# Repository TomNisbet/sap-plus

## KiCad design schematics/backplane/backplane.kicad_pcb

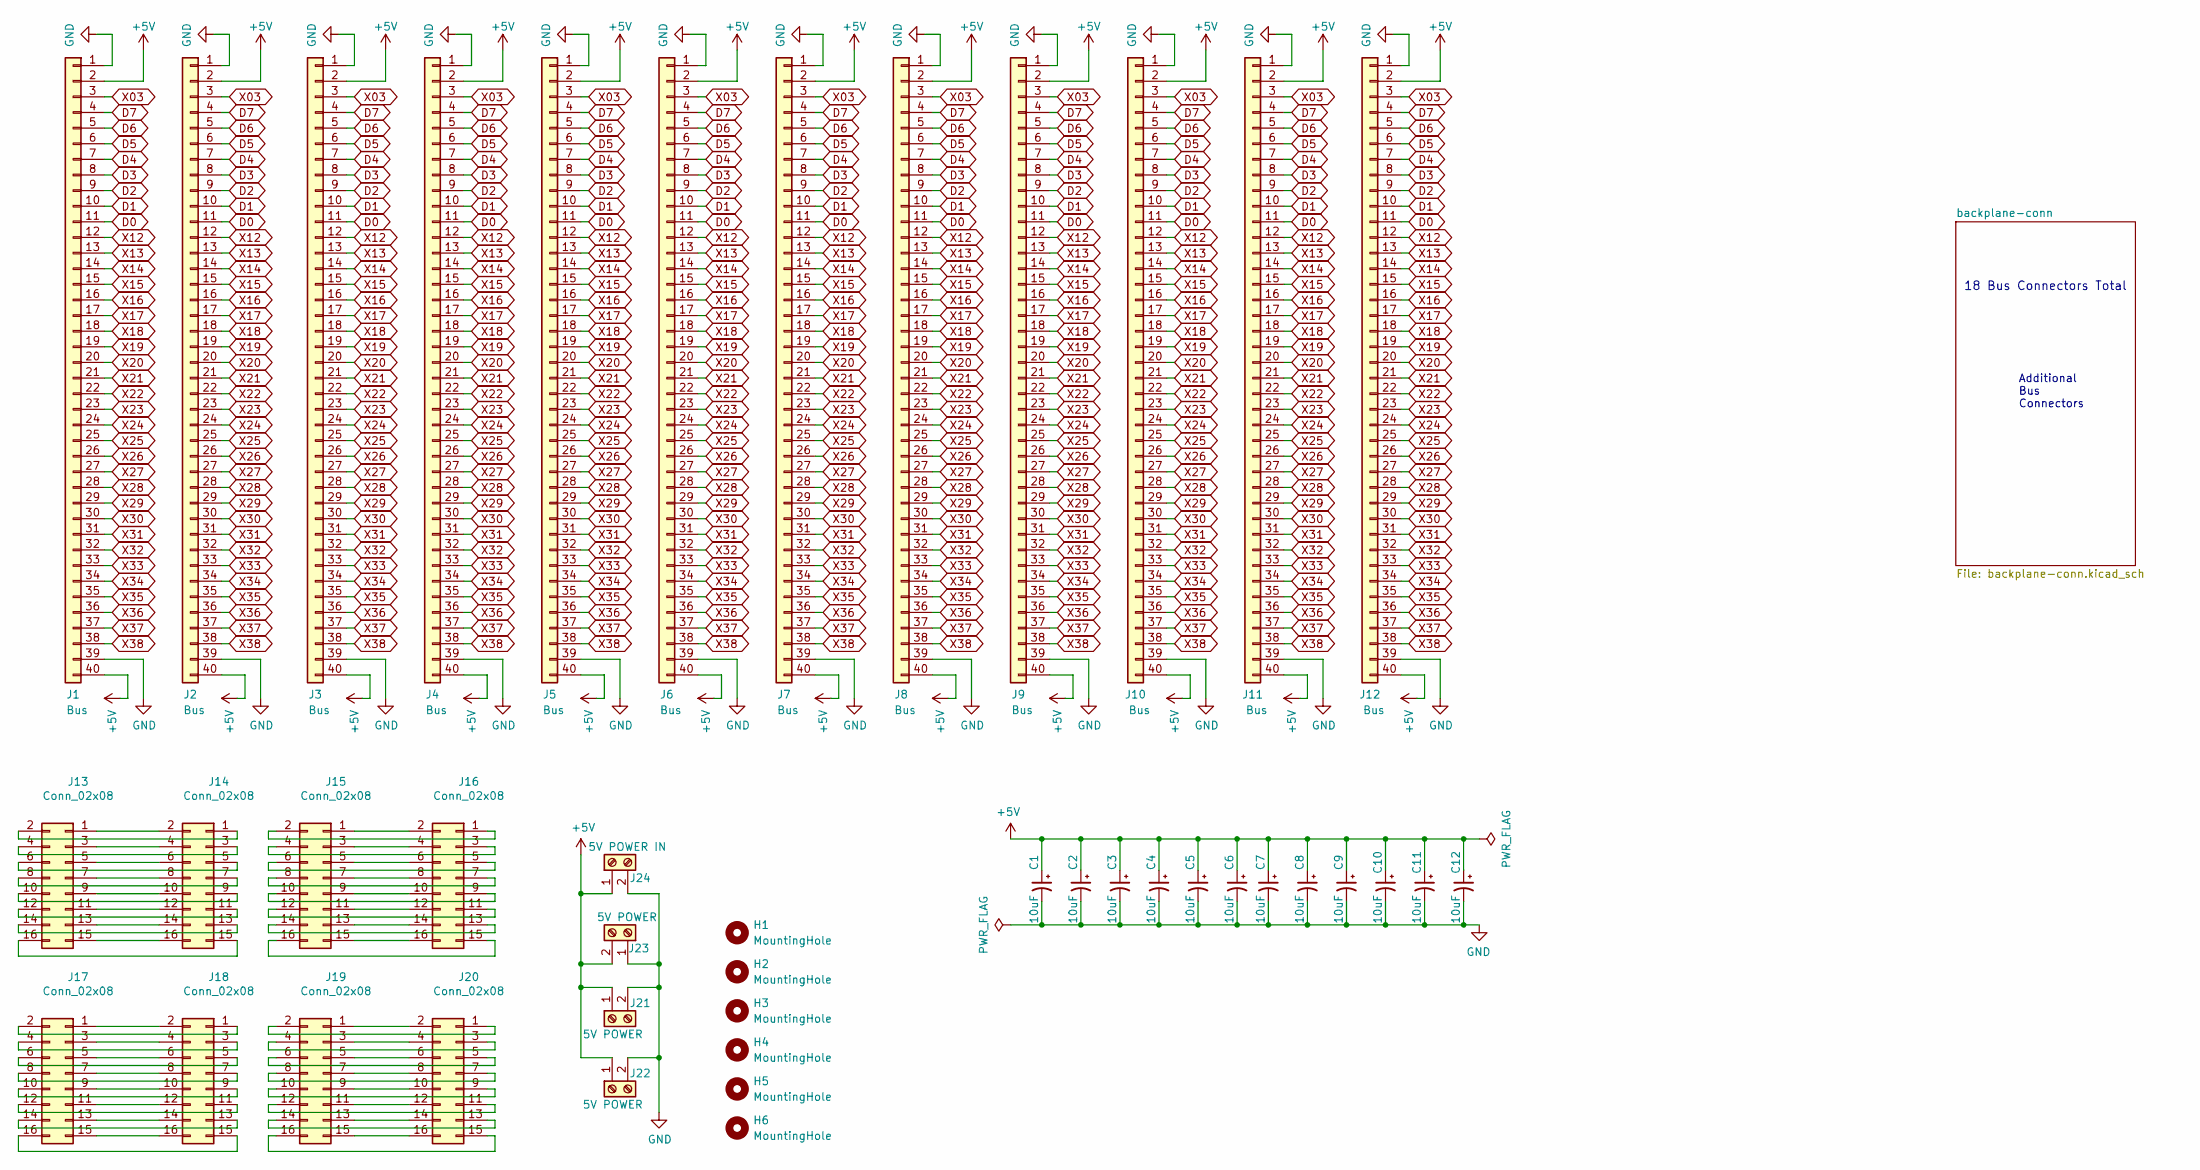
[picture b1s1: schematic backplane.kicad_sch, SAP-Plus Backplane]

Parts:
C1, C2, C3, C4, C5, C6, C7, C8, C9, C10, C11, C12: 10uF; C_Radial_D4.0mm_H5.0mm_P1.50mm
H1, H2, H3, H4, H5, H6: MountingHole; MountingHole_3.2mm_M3
J1, J2, J3, J4, J5, J6, J7, J8, J9, J10, J11, J12: Bus; PinSocket_1x40_P2.54mm_Vertical
J13, J14, J15, J16, J17, J18, J19, J20: Conn_02x08; PinSocket_2x08_P2.54mm_Vertical
J21, J22, J23: 5V POWER; TerminalBlock_RND_205-00012_1x02_P5.00mm_Horizontal
J24: 5V POWER IN; BarrelJack_Wuerth_6941xx301002

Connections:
+5V: C1.1, C2.1, C3.1, C4.1, C5.1, C6.1, C7.1, C8.1, C9.1, C10.1, C11.1, C12.1, J1.2, J1.40, J2.2, J2.40, J3.2, J3.40, J4.2, J4.40, J5.2, J5.40, J6.2, J6.40, J7.2, J7.40, J8.2, J8.40, J9.2, J9.40, J10.2, J10.40, J11.2, J11.40, J12.2, J12.40, J21.1, J22.1, J23.2, J24.1
D0: J1.11, J2.11, J3.11, J4.11, J5.11, J6.11, J7.11, J8.11, J9.11, J10.11, J11.11, J12.11
D1: J1.10, J2.10, J3.10, J4.10, J5.10, J6.10, J7.10, J8.10, J9.10, J10.10, J11.10, J12.10
D2: J1.9, J2.9, J3.9, J4.9, J5.9, J6.9, J7.9, J8.9, J9.9, J10.9, J11.9, J12.9
D3: J1.8, J2.8, J3.8, J4.8, J5.8, J6.8, J7.8, J8.8, J9.8, J10.8, J11.8, J12.8
D4: J1.7, J2.7, J3.7, J4.7, J5.7, J6.7, J7.7, J8.7, J9.7, J10.7, J11.7, J12.7
D5: J1.6, J2.6, J3.6, J4.6, J5.6, J6.6, J7.6, J8.6, J9.6, J10.6, J11.6, J12.6
D6: J1.5, J2.5, J3.5, J4.5, J5.5, J6.5, J7.5, J8.5, J9.5, J10.5, J11.5, J12.5
D7: J1.4, J2.4, J3.4, J4.4, J5.4, J6.4, J7.4, J8.4, J9.4, J10.4, J11.4, J12.4
GND: C1.2, C2.2, C3.2, C4.2, C5.2, C6.2, C7.2, C8.2, C9.2, C10.2, C11.2, C12.2, J1.1, J1.39, J2.1, J2.39, J3.1, J3.39, J4.1, J4.39, J5.1, J5.39, J6.1, J6.39, J7.1, J7.39, J8.1, J8.39, J9.1, J9.39, J10.1, J10.39, J11.1, J11.39, J12.1, J12.39, J21.2, J22.2, J23.1, J24.2
unnamed: J13.1, J14.2
unnamed: J13.2, J14.1
unnamed: J13.3, J14.4
unnamed: J13.4, J14.3
unnamed: J13.5, J14.6
unnamed: J13.6, J14.5
unnamed: J13.7, J14.8
unnamed: J13.8, J14.7
unnamed: J13.9, J14.10
unnamed: J13.10, J14.9
unnamed: J13.11, J14.12
unnamed: J13.12, J14.11
unnamed: J13.13, J14.14
unnamed: J13.14, J14.13
unnamed: J13.15, J14.16
unnamed: J13.16, J14.15
unnamed: J15.1, J16.2
unnamed: J15.2, J16.1
unnamed: J15.3, J16.4
unnamed: J15.4, J16.3
unnamed: J15.5, J16.6
unnamed: J15.6, J16.5
unnamed: J15.7, J16.8
unnamed: J15.8, J16.7
unnamed: J15.9, J16.10
unnamed: J15.10, J16.9
unnamed: J15.11, J16.12
unnamed: J15.12, J16.11
unnamed: J15.13, J16.14
unnamed: J15.14, J16.13
unnamed: J15.15, J16.16
unnamed: J15.16, J16.15
unnamed: J17.1, J18.2
unnamed: J17.2, J18.1
unnamed: J17.3, J18.4
unnamed: J17.4, J18.3
unnamed: J17.5, J18.6
unnamed: J17.6, J18.5
unnamed: J17.7, J18.8
unnamed: J17.8, J18.7
unnamed: J17.9, J18.10
unnamed: J17.10, J18.9
unnamed: J17.11, J18.12
unnamed: J17.12, J18.11
unnamed: J17.13, J18.14
unnamed: J17.14, J18.13
unnamed: J17.15, J18.16
unnamed: J17.16, J18.15
unnamed: J19.1, J20.2
unnamed: J19.2, J20.1
unnamed: J19.3, J20.4
unnamed: J19.4, J20.3
unnamed: J19.5, J20.6
unnamed: J19.6, J20.5
unnamed: J19.7, J20.8
unnamed: J19.8, J20.7
unnamed: J19.9, J20.10
unnamed: J19.10, J20.9
unnamed: J19.11, J20.12
unnamed: J19.12, J20.11
unnamed: J19.13, J20.14
unnamed: J19.14, J20.13
unnamed: J19.15, J20.16
unnamed: J19.16, J20.15
X03: J1.3, J2.3, J3.3, J4.3, J5.3, J6.3, J7.3, J8.3, J9.3, J10.3, J11.3, J12.3
X12: J1.12, J2.12, J3.12, J4.12, J5.12, J6.12, J7.12, J8.12, J9.12, J10.12, J11.12, J12.12
X13: J1.13, J2.13, J3.13, J4.13, J5.13, J6.13, J7.13, J8.13, J9.13, J10.13, J11.13, J12.13
X14: J1.14, J2.14, J3.14, J4.14, J5.14, J6.14, J7.14, J8.14, J9.14, J10.14, J11.14, J12.14
X15: J1.15, J2.15, J3.15, J4.15, J5.15, J6.15, J7.15, J8.15, J9.15, J10.15, J11.15, J12.15
X16: J1.16, J2.16, J3.16, J4.16, J5.16, J6.16, J7.16, J8.16, J9.16, J10.16, J11.16, J12.16
X17: J1.17, J2.17, J3.17, J4.17, J5.17, J6.17, J7.17, J8.17, J9.17, J10.17, J11.17, J12.17
X18: J1.18, J2.18, J3.18, J4.18, J5.18, J6.18, J7.18, J8.18, J9.18, J10.18, J11.18, J12.18
X19: J1.19, J2.19, J3.19, J4.19, J5.19, J6.19, J7.19, J8.19, J9.19, J10.19, J11.19, J12.19
X20: J1.20, J2.20, J3.20, J4.20, J5.20, J6.20, J7.20, J8.20, J9.20, J10.20, J11.20, J12.20
X21: J1.21, J2.21, J3.21, J4.21, J5.21, J6.21, J7.21, J8.21, J9.21, J10.21, J11.21, J12.21
X22: J1.22, J2.22, J3.22, J4.22, J5.22, J6.22, J7.22, J8.22, J9.22, J10.22, J11.22, J12.22
X23: J1.23, J2.23, J3.23, J4.23, J5.23, J6.23, J7.23, J8.23, J9.23, J10.23, J11.23, J12.23
X24: J1.24, J2.24, J3.24, J4.24, J5.24, J6.24, J7.24, J8.24, J9.24, J10.24, J11.24, J12.24
X25: J1.25, J2.25, J3.25, J4.25, J5.25, J6.25, J7.25, J8.25, J9.25, J10.25, J11.25, J12.25
X26: J1.26, J2.26, J3.26, J4.26, J5.26, J6.26, J7.26, J8.26, J9.26, J10.26, J11.26, J12.26
X27: J1.27, J2.27, J3.27, J4.27, J5.27, J6.27, J7.27, J8.27, J9.27, J10.27, J11.27, J12.27
X28: J1.28, J2.28, J3.28, J4.28, J5.28, J6.28, J7.28, J8.28, J9.28, J10.28, J11.28, J12.28
X29: J1.29, J2.29, J3.29, J4.29, J5.29, J6.29, J7.29, J8.29, J9.29, J10.29, J11.29, J12.29
X30: J1.30, J2.30, J3.30, J4.30, J5.30, J6.30, J7.30, J8.30, J9.30, J10.30, J11.30, J12.30
X31: J1.31, J2.31, J3.31, J4.31, J5.31, J6.31, J7.31, J8.31, J9.31, J10.31, J11.31, J12.31
X32: J1.32, J2.32, J3.32, J4.32, J5.32, J6.32, J7.32, J8.32, J9.32, J10.32, J11.32, J12.32
X33: J1.33, J2.33, J3.33, J4.33, J5.33, J6.33, J7.33, J8.33, J9.33, J10.33, J11.33, J12.33
X34: J1.34, J2.34, J3.34, J4.34, J5.34, J6.34, J7.34, J8.34, J9.34, J10.34, J11.34, J12.34
X35: J1.35, J2.35, J3.35, J4.35, J5.35, J6.35, J7.35, J8.35, J9.35, J10.35, J11.35, J12.35
X36: J1.36, J2.36, J3.36, J4.36, J5.36, J6.36, J7.36, J8.36, J9.36, J10.36, J11.36, J12.36
X37: J1.37, J2.37, J3.37, J4.37, J5.37, J6.37, J7.37, J8.37, J9.37, J10.37, J11.37, J12.37
X38: J1.38, J2.38, J3.38, J4.38, J5.38, J6.38, J7.38, J8.38, J9.38, J10.38, J11.38, J12.38

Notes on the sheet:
Additional Bus Connectors
18 Bus Connectors Total

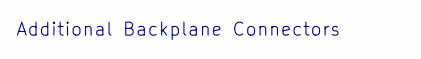
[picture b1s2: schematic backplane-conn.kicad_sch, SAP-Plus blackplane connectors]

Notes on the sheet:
Additional Backplane Connectors

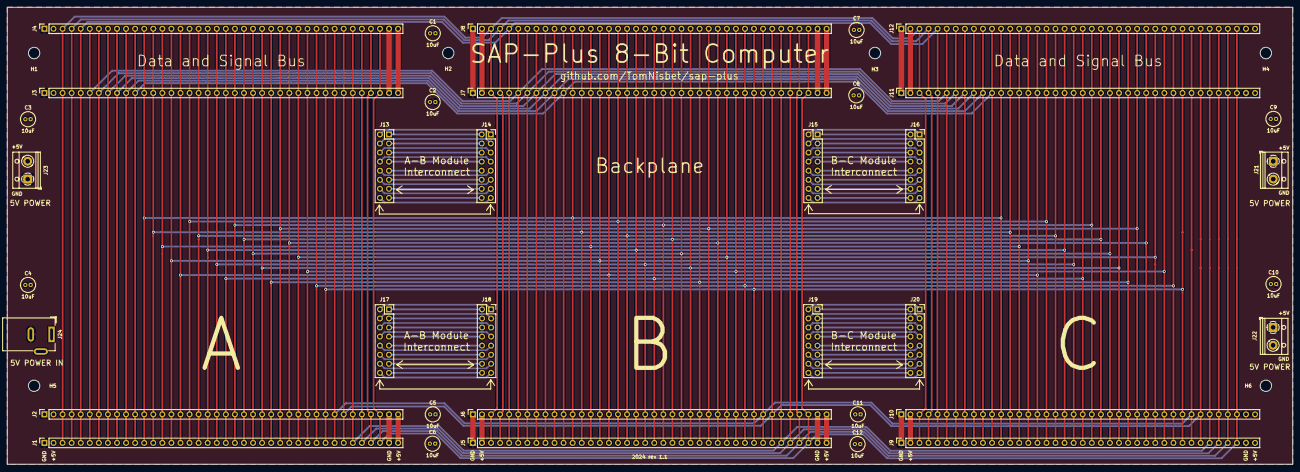
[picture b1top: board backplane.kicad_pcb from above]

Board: 2 copper layers, 360.0 x 128.0 mm, 42 parts (0 on the bottom side), 102 nets.

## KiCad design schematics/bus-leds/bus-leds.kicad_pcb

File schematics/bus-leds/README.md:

# Bus Connector with LEDs schematics

created with KiCad 8.0

## Changelog

### 1.0

* Initial version

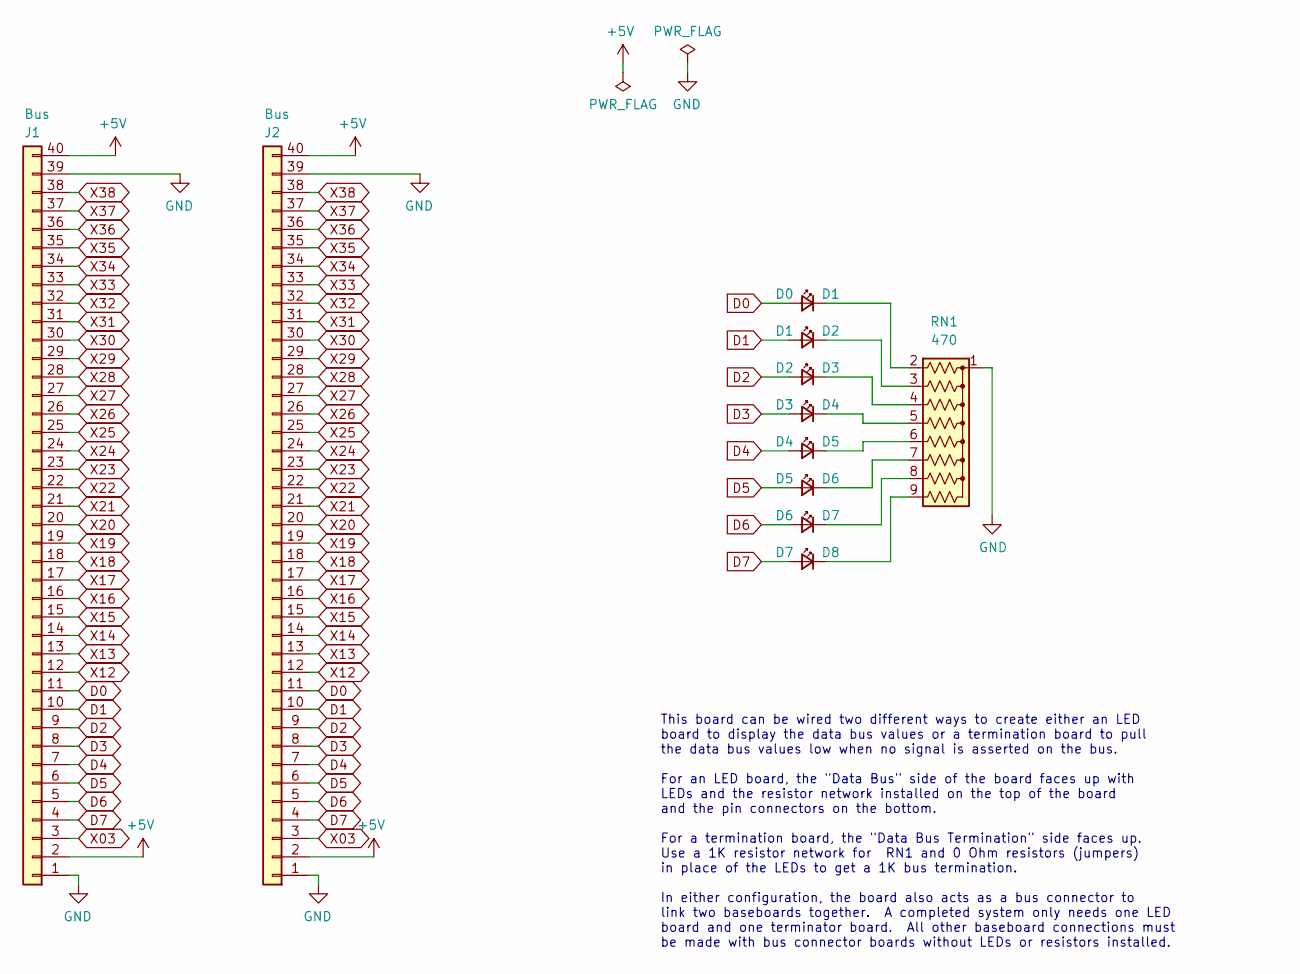
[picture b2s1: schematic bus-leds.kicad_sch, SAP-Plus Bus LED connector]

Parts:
D1: D0; LED_D3.0mm
D2: D1; LED_D3.0mm
D3: D2; LED_D3.0mm
D4: D3; LED_D3.0mm
D5: D4; LED_D3.0mm
D6: D5; LED_D3.0mm
D7: D6; LED_D3.0mm
D8: D7; LED_D3.0mm
J1, J2: Bus; PinHeader_1x40_P2.54mm_Vertical
RN1: 470; R_Array_SIP9

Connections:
+5V: J1.2, J1.40, J2.2, J2.40
D0: D1.2 (A), J1.11, J2.11
D1: D2.2 (A), J1.10, J2.10
D2: D3.2 (A), J1.9, J2.9
D3: D4.2 (A), J1.8, J2.8
D4: D5.2 (A), J1.7, J2.7
D5: D6.2 (A), J1.6, J2.6
D6: D7.2 (A), J1.5, J2.5
D7: D8.2 (A), J1.4, J2.4
GND: J1.1, J1.39, J2.1, J2.39, RN1.1 (common)
unnamed: D1.1 (K), RN1.2 (R1)
unnamed: D2.1 (K), RN1.3 (R2)
unnamed: D3.1 (K), RN1.4 (R3)
unnamed: D4.1 (K), RN1.5 (R4)
unnamed: D5.1 (K), RN1.6 (R5)
unnamed: D6.1 (K), RN1.7 (R6)
unnamed: D7.1 (K), RN1.8 (R7)
unnamed: D8.1 (K), RN1.9 (R8)
X03: J1.3, J2.3
X12: J1.12, J2.12
X13: J1.13, J2.13
X14: J1.14, J2.14
X15: J1.15, J2.15
X16: J1.16, J2.16
X17: J1.17, J2.17
X18: J1.18, J2.18
X19: J1.19, J2.19
X20: J1.20, J2.20
X21: J1.21, J2.21
X22: J1.22, J2.22
X23: J1.23, J2.23
X24: J1.24, J2.24
X25: J1.25, J2.25
X26: J1.26, J2.26
X27: J1.27, J2.27
X28: J1.28, J2.28
X29: J1.29, J2.29
X30: J1.30, J2.30
X31: J1.31, J2.31
X32: J1.32, J2.32
X33: J1.33, J2.33
X34: J1.34, J2.34
X35: J1.35, J2.35
X36: J1.36, J2.36
X37: J1.37, J2.37
X38: J1.38, J2.38

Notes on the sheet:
This board can be wired two different ways to create either an LED board to display the data bus values or a termination board to pull the data bus values low when no signal is asserted on the bus. For an LED board, the "Data Bus" side of the board faces up with LEDs and the resistor network instal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

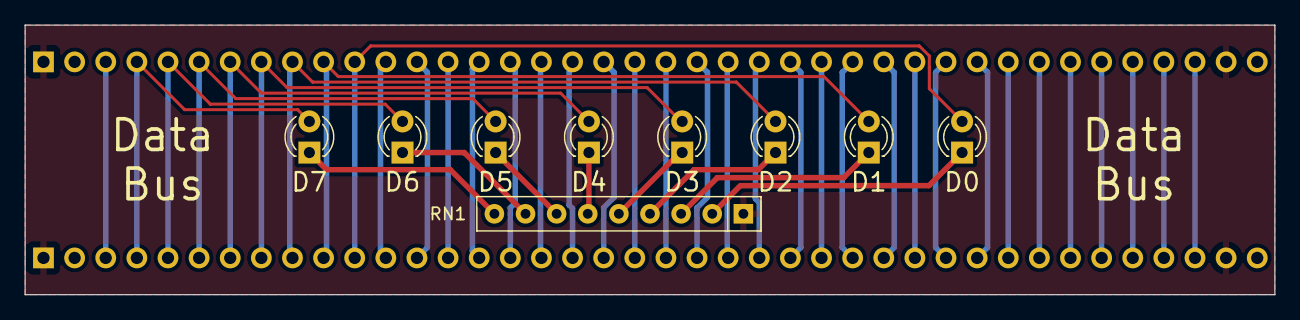
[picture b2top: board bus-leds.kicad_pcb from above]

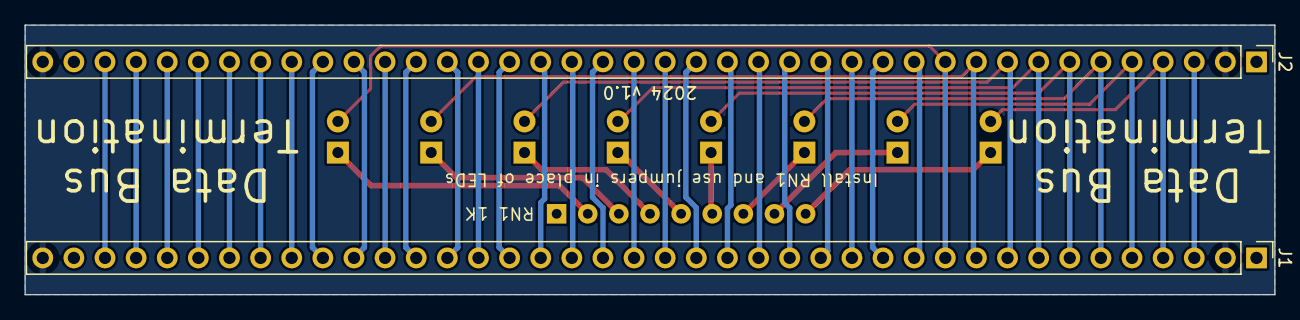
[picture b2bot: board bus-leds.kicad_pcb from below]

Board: 2 copper layers, 102.0 x 22.0 mm, 11 parts (2 on the bottom side), 46 nets.

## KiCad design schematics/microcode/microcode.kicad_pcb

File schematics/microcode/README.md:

# Microcode Module schematics

created with KiCad 8.0

## Changelog

### 1.1

* Add labels module interconnect headers

### 1.0

* Initial version

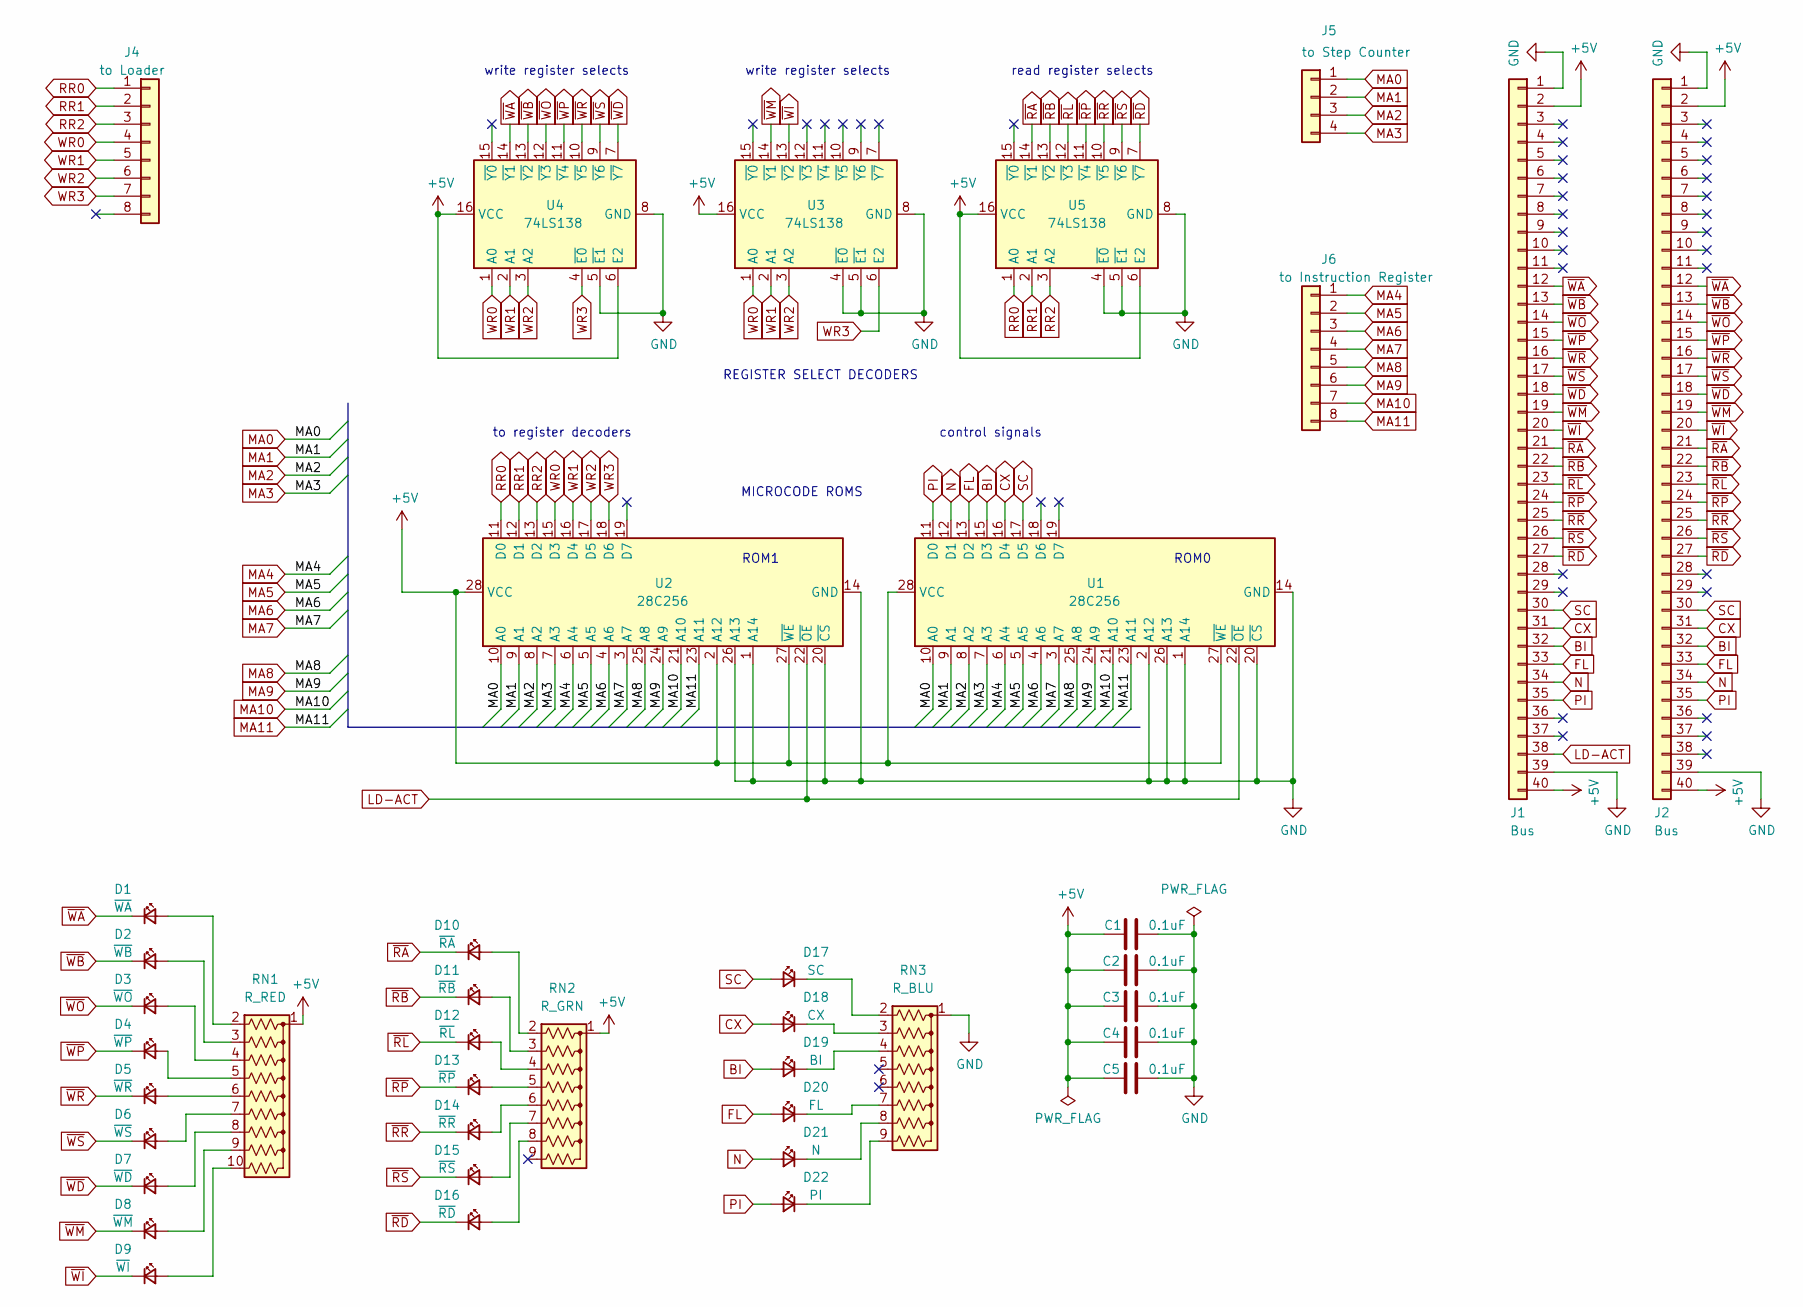
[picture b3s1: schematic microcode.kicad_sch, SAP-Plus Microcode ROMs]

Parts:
C1, C2, C3, C4, C5: 0.1uF; C_Disc_D3.0mm_W1.6mm_P2.50mm
D1: ~{WA}; LED_D3.0mm
D2: ~{WB}; LED_D3.0mm
D3: ~{WO}; LED_D3.0mm
D4: ~{WP}; LED_D3.0mm
D5: ~{WR}; LED_D3.0mm
D6: ~{WS}; LED_D3.0mm
D7: ~{WD}; LED_D3.0mm
D8: ~{WM}; LED_D3.0mm
D9: ~{WI}; LED_D3.0mm
D10: ~{RA}; LED_D3.0mm
D11: ~{RB}; LED_D3.0mm
D12: ~{RL}; LED_D3.0mm
D13: ~{RP}; LED_D3.0mm
D14: ~{RR}; LED_D3.0mm
D15: ~{RS}; LED_D3.0mm
D16: ~{RD}; LED_D3.0mm
D17: SC; LED_D3.0mm
D18: CX; LED_D3.0mm
D19: BI; LED_D3.0mm
D20: FL; LED_D3.0mm
D21: N; LED_D3.0mm
D22: PI; LED_D3.0mm
J1, J2: Bus; PinHeader_1x40_P2.54mm_Vertical
J4: to Loader; PinHeader_1x08_P2.54mm_Vertical
J5: to Step Counter; PinHeader_1x04_P2.54mm_Vertical
J6: to Instruction Register; PinHeader_1x08_P2.54mm_Vertical
RN1: R_RED; R_Array_SIP10
RN2: R_GRN; R_Array_SIP9
RN3: R_BLU; R_Array_SIP9
U1, U2: 28C256; DIP-28_W15.24mm_Socket
U3, U4, U5: 74LS138; DIP-16_W7.62mm

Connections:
+5V: C1.2, C2.2, C3.2, C4.2, C5.2, J1.2, J1.40, J2.2, J2.40, RN1.1 (common), RN2.1 (common), U1.27 (~WE), U1.28 (VCC), U2.2 (A12), U2.27 (~WE), U2.28 (VCC), U3.16 (VCC), U4.6 (E2), U4.16 (VCC), U5.6 (E2), U5.16 (VCC)
BI: D19.2 (A), J1.32, J2.32, U1.15 (D3)
CX: D18.2 (A), J1.31, J2.31, U1.16 (D4)
FL: D20.2 (A), J1.33, J2.33, U1.13 (D2)
GND: C1.1, C2.1, C3.1, C4.1, C5.1, J1.1, J1.39, J2.1, J2.39, RN3.1 (common), U1.1 (A14), U1.2 (A12), U1.14 (GND), U1.20 (~CS), U1.26 (A13), U2.1 (A14), U2.14 (GND), U2.20 (~CS), U2.26 (A13), U3.4 (~E0), U3.5 (~E1), U3.8 (GND), U4.5 (~E1), U4.8 (GND), U5.4 (~E0), U5.5 (~E1), U5.8 (GND)
LD-ACT: J1.38, U1.22 (~OE), U2.22 (~OE)
MA0: J5.1, U1.10 (A0), U2.10 (A0)
MA1: J5.2, U1.9 (A1), U2.9 (A1)
MA2: J5.3, U1.8 (A2), U2.8 (A2)
MA3: J5.4, U1.7 (A3), U2.7 (A3)
MA4: J6.1, U1.6 (A4), U2.6 (A4)
MA5: J6.2, U1.5 (A5), U2.5 (A5)
MA6: J6.3, U1.4 (A6), U2.4 (A6)
MA7: J6.4, U1.3 (A7), U2.3 (A7)
MA8: J6.5, U1.25 (A8), U2.25 (A8)
MA9: J6.6, U1.24 (A9), U2.24 (A9)
MA10: J6.7, U1.21 (A10), U2.21 (A10)
MA11: J6.8, U1.23 (A11), U2.23 (A11)
N: D21.2 (A), J1.34, J2.34, U1.12 (D1)
unnamed: D1.2 (A), RN1.2 (R1)
unnamed: D2.2 (A), RN1.3 (R2)
unnamed: D3.2 (A), RN1.4 (R3)
unnamed: D4.2 (A), RN1.5 (R4)
unnamed: D5.2 (A), RN1.6 (R5)
unnamed: D6.2 (A), RN1.7 (R6)
unnamed: D7.2 (A), RN1.8 (R7)
unnamed: D8.2 (A), RN1.9 (R8)
unnamed: D9.2 (A), RN1.10 (R9)
unnamed: D10.2 (A), RN2.2 (R1)
unnamed: D11.2 (A), RN2.3 (R2)
unnamed: D12.2 (A), RN2.4 (R3)
unnamed: D13.2 (A), RN2.5 (R4)
unnamed: D14.2 (A), RN2.6 (R5)
unnamed: D15.2 (A), RN2.7 (R6)
unnamed: D16.2 (A), RN2.8 (R7)
unnamed: D17.1 (K), RN3.2 (R1)
unnamed: D18.1 (K), RN3.3 (R2)
unnamed: D19.1 (K), RN3.4 (R3)
unnamed: D20.1 (K), RN3.7 (R6)
unnamed: D21.1 (K), RN3.8 (R7)
unnamed: D22.1 (K), RN3.9 (R8)
PI: D22.2 (A), J1.35, J2.35, U1.11 (D0)
RR0: J4.1, U2.11 (D0), U5.1 (A0)
RR1: J4.2, U2.12 (D1), U5.2 (A1)
RR2: J4.3, U2.13 (D2), U5.3 (A2)
SC: D17.2 (A), J1.30, J2.30, U1.17 (D5)
WR0: J4.4, U2.15 (D3), U3.1 (A0), U4.1 (A0)
WR1: J4.5, U2.16 (D4), U3.2 (A1), U4.2 (A1)
WR2: J4.6, U2.17 (D5), U3.3 (A2), U4.3 (A2)
WR3: J4.7, U2.18 (D6), U3.6 (E2), U4.4 (~E0)
~RA: D10.1 (K), J1.21, J2.21, U5.14 (~Y1)
~RB: D11.1 (K), J1.22, J2.22, U5.13 (~Y2)
~RD: D16.1 (K), J1.27, J2.27, U5.7 (~Y7)
~RL: D12.1 (K), J1.23, J2.23, U5.12 (~Y3)
~RP: D13.1 (K), J1.24, J2.24, U5.11 (~Y4)
~RR: D14.1 (K), J1.25, J2.25, U5.10 (~Y5)
~RS: D15.1 (K), J1.26, J2.26, U5.9 (~Y6)
~WA: D1.1 (K), J1.12, J2.12, U4.14 (~Y1)
~WB: D2.1 (K), J1.13, J2.13, U4.13 (~Y2)
~WD: D7.1 (K), J1.18, J2.18, U4.7 (~Y7)
~WI: D9.1 (K), J1.20, J2.20, U3.13 (~Y2)
~WM: D8.1 (K), J1.19, J2.19, U3.14 (~Y1)
~WO: D3.1 (K), J1.14, J2.14, U4.12 (~Y3)
~WP: D4.1 (K), J1.15, J2.15, U4.11 (~Y4)
~WR: D5.1 (K), J1.16, J2.16, U4.10 (~Y5)
~WS: D6.1 (K), J1.17, J2.17, U4.9 (~Y6)

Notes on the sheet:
read register selects
to register decoders
write register selects
REGISTER SELECT DECODERS
control signals
MICROCODE ROMS
ROM1
ROM0

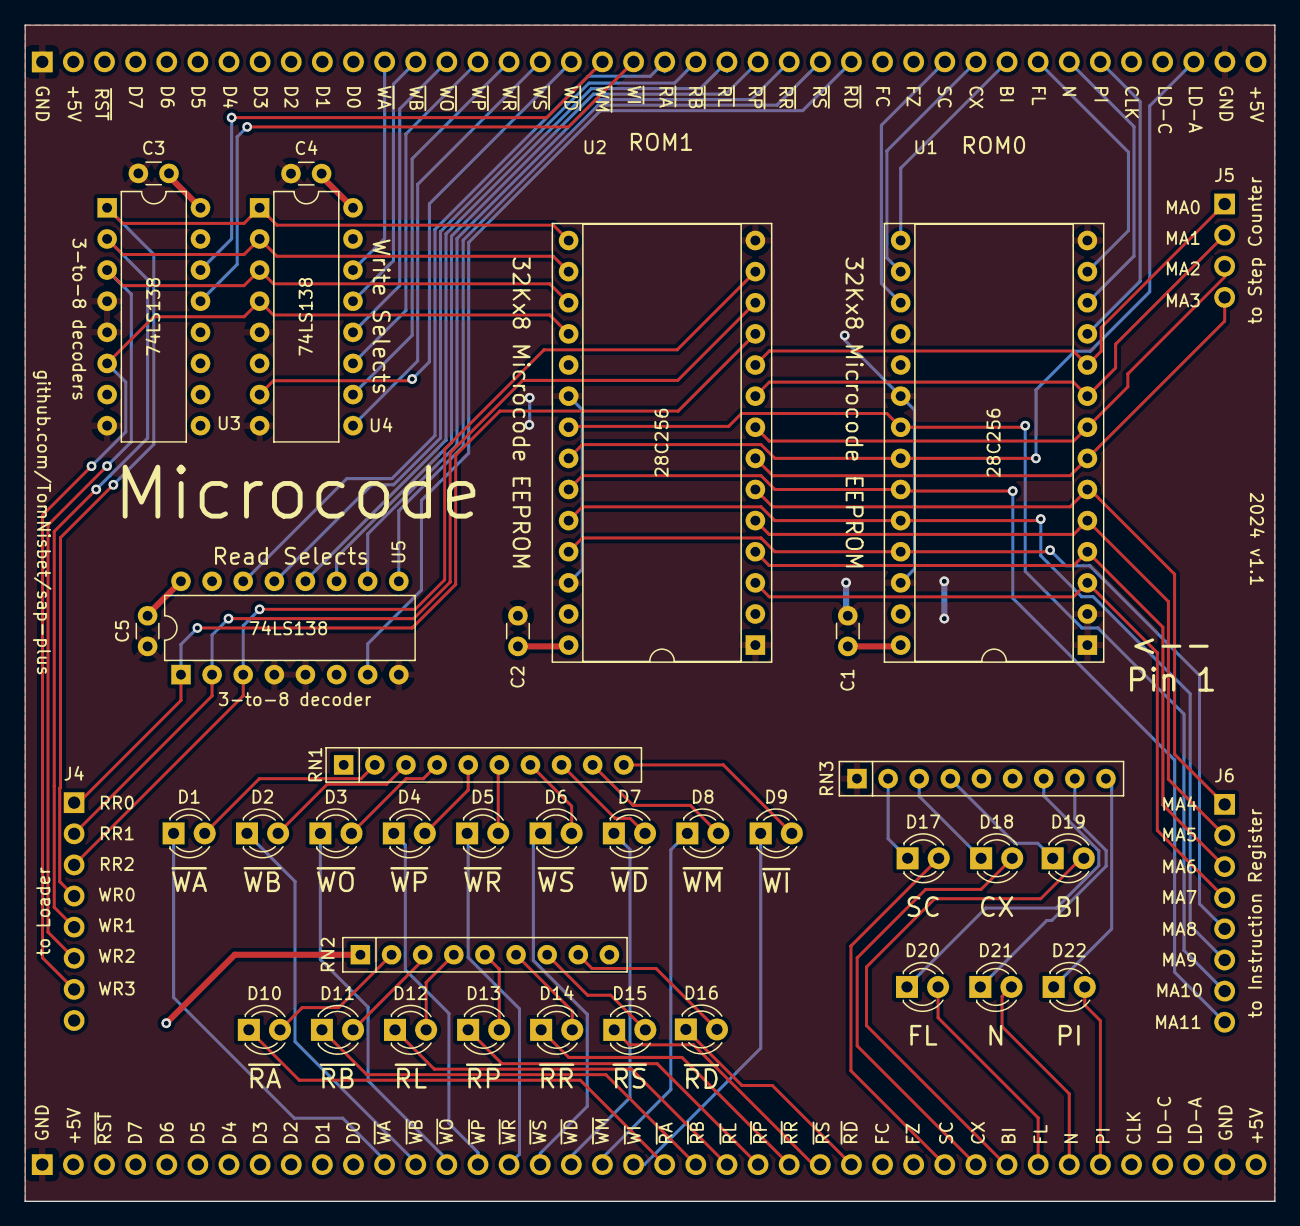
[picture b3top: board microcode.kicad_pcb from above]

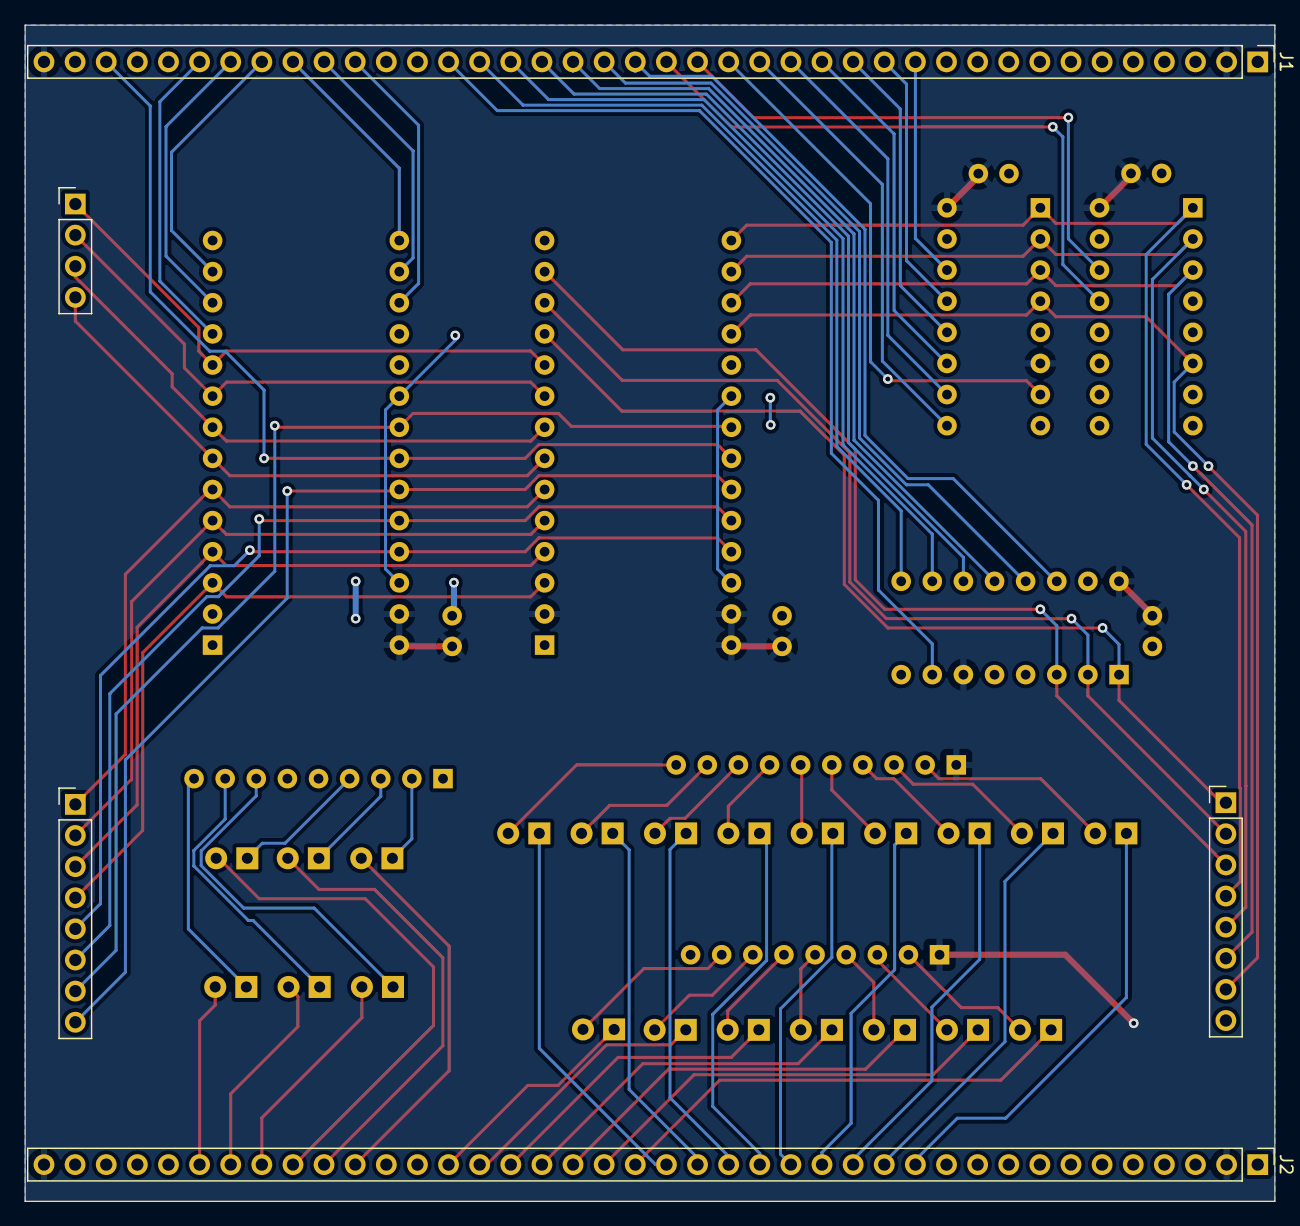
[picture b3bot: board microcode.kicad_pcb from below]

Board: 2 copper layers, 102.0 x 96.0 mm, 40 parts (5 on the bottom side), 66 nets.

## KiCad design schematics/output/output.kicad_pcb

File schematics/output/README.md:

# Output Register Module schematics

created with KiCad 8.0

## Changelog

### 1.0

* Initial version

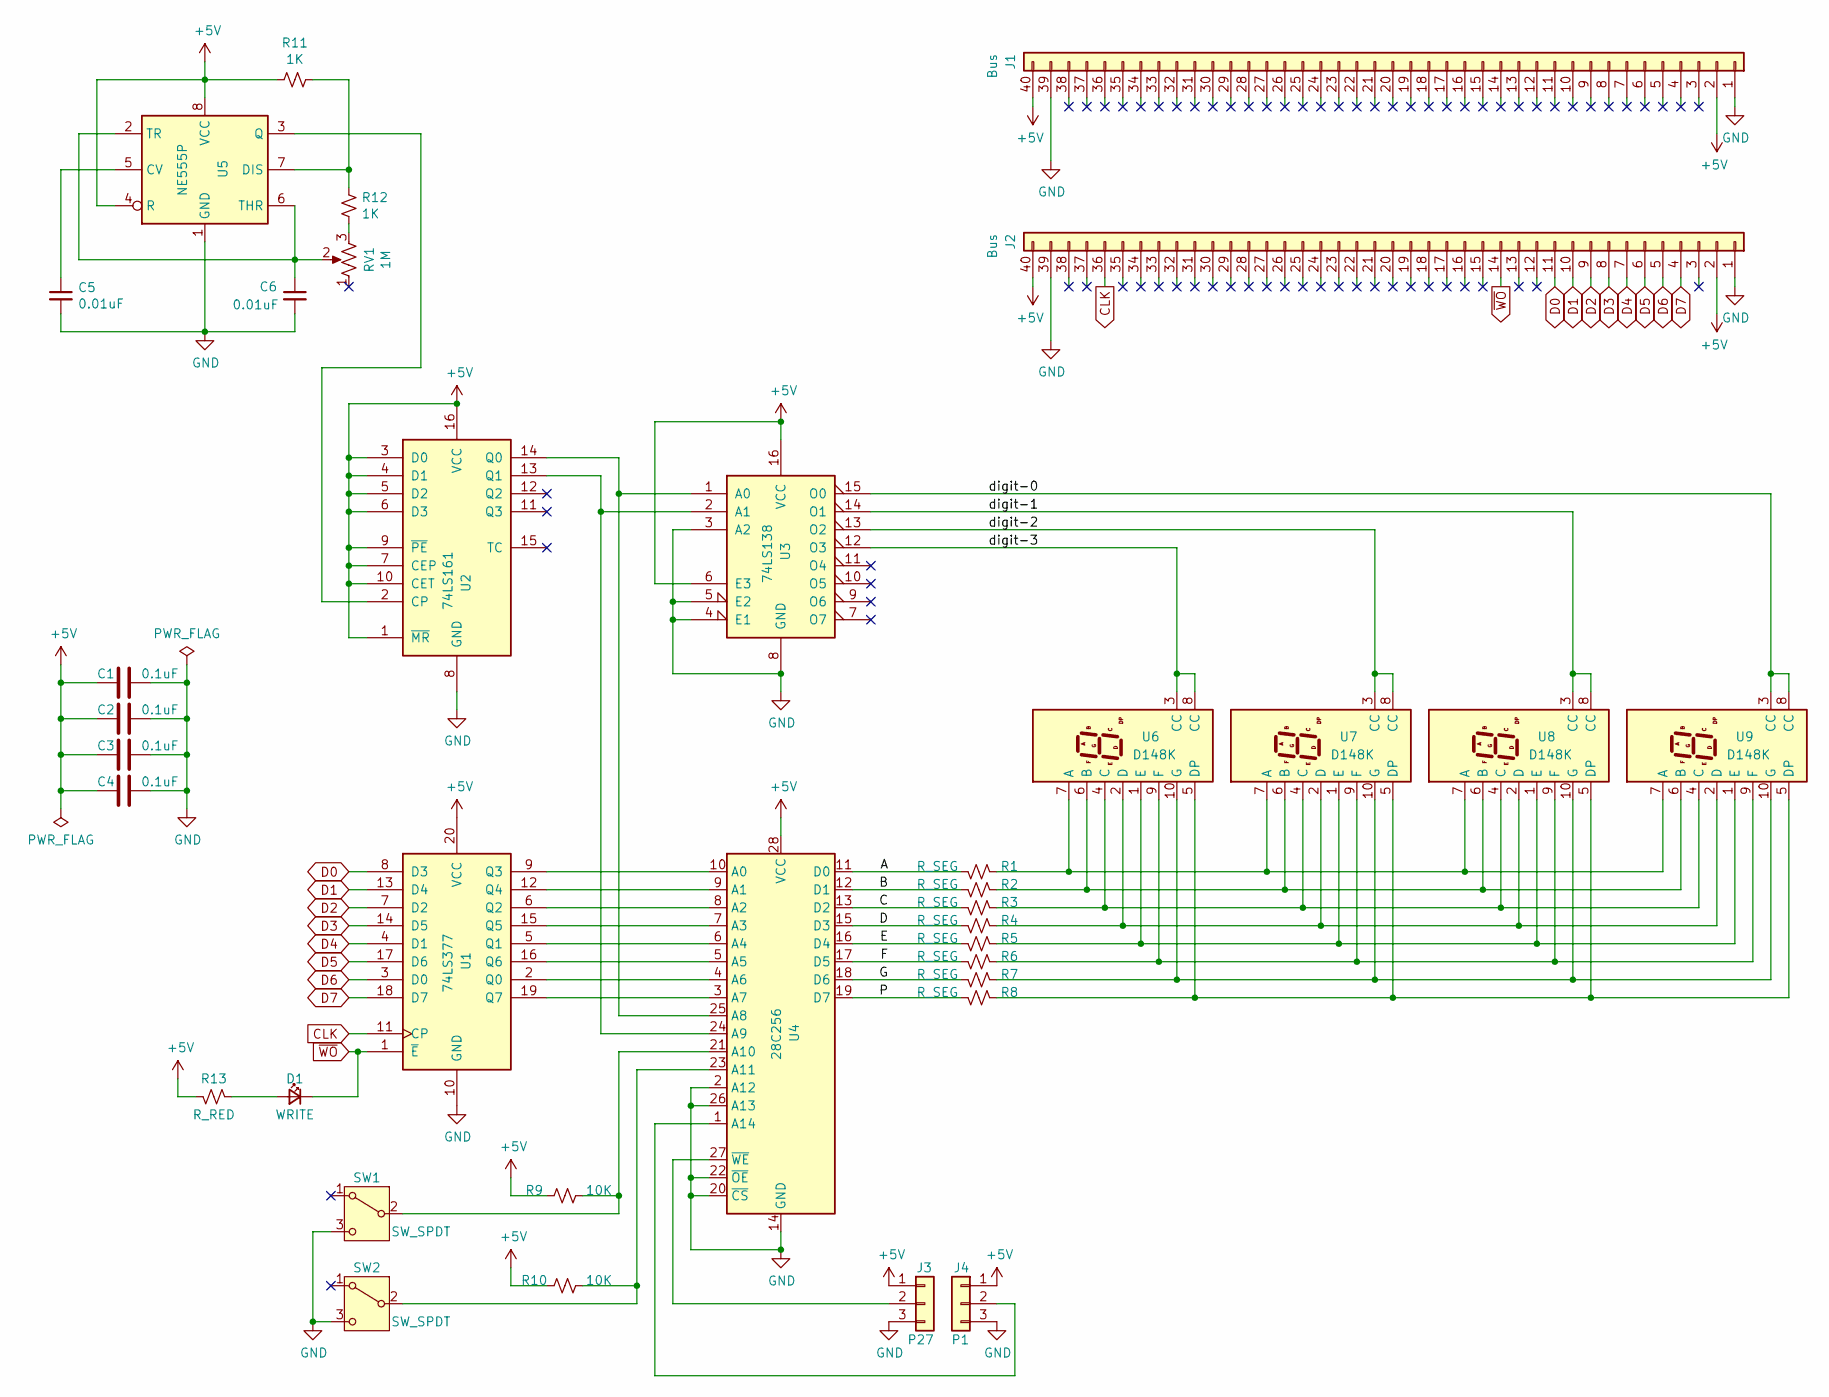
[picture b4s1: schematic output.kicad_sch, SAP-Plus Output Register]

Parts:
C1, C2, C3, C4: 0.1uF; C_Disc_D3.0mm_W1.6mm_P2.50mm
C5, C6: 0.01uF; C_Disc_D3.0mm_W1.6mm_P2.50mm
D1: WRITE; LED_D3.0mm
J1, J2: Bus; PinHeader_1x40_P2.54mm_Vertical
J3: P27; PinHeader_1x03_P2.54mm_Vertical
J4: P1; PinHeader_1x03_P2.54mm_Vertical
R1, R2, R3, R4, R5, R6, R7, R8: R_SEG; R_Axial_DIN0207_L6.3mm_D2.5mm_P10.16mm_Horizontal
R9, R10: 10K; R_Axial_DIN0207_L6.3mm_D2.5mm_P10.16mm_Horizontal
R11, R12: 1K; R_Axial_DIN0207_L6.3mm_D2.5mm_P10.16mm_Horizontal
R13: R_RED; R_Axial_DIN0207_L6.3mm_D2.5mm_P10.16mm_Horizontal
RV1: 1M; Potentiometer_Bourns_3386F_Vertical
SW1, SW2: SW_SPDT; PinHeader_1x03_P2.54mm_Vertical
U1: 74LS377; DIP-20_W7.62mm
U2: 74LS161; DIP-16_W7.62mm
U3: 74LS138; DIP-16_W7.62mm
U4: 28C256; DIP-28_W15.24mm
U5: NE555P; DIP-8_W7.62mm
U6, U7, U8, U9: D148K; D1X8K

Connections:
+5V: C1.2, C2.2, C3.2, C4.2, J1.2, J1.40, J2.2, J2.40, J3.1, J4.1, R9.1, R10.1, R11.2, R13.2, U1.20 (VCC), U2.1 (~MR), U2.3 (D0), U2.4 (D1), U2.5 (D2), U2.6 (D3), U2.7 (CEP), U2.9 (~PE), U2.10 (CET), U2.16 (VCC), U3.6 (E3), U3.16 (VCC), U4.28 (VCC), U5.4 (R), U5.8 (VCC)
/A: R1.2, U4.11 (D0)
/B: R2.2, U4.12 (D1)
/C: R3.2, U4.13 (D2)
/D: R4.2, U4.15 (D3)
/E: R5.2, U4.16 (D4)
/F: R6.2, U4.17 (D5)
/G: R7.2, U4.18 (D6)
/P: R8.2, U4.19 (D7)
/digit-0: U3.15 (O0), U9.3 (CC), U9.8 (CC)
/digit-1: U3.14 (O1), U8.3 (CC), U8.8 (CC)
/digit-2: U3.13 (O2), U7.3 (CC), U7.8 (CC)
/digit-3: U3.12 (O3), U6.3 (CC), U6.8 (CC)
CLK: J2.36, U1.11 (CP)
D0: J2.11, U1.8 (D3)
D1: J2.10, U1.13 (D4)
D2: J2.9, U1.7 (D2)
D3: J2.8, U1.14 (D5)
D4: J2.7, U1.4 (D1)
D5: J2.6, U1.17 (D6)
D6: J2.5, U1.3 (D0)
D7: J2.4, U1.18 (D7)
GND: C1.1, C2.1, C3.1, C4.1, C5.2, C6.2, J1.1, J1.39, J2.1, J2.39, J3.3, J4.3, SW1.3 (C), SW2.3 (C), U1.10 (GND), U2.8 (GND), U3.3 (A2), U3.4 (E1), U3.5 (E2), U3.8 (GND), U4.2 (A12), U4.14 (GND), U4.20 (~CS), U4.22 (~OE), U4.26 (A13), U5.1 (GND)
unnamed: D1.2 (A), R13.1
unnamed: J3.2, U4.27 (~WE)
unnamed: J4.2, U4.1 (A14)
unnamed: R12.1, RV1.3
unnamed: R9.2, SW1.2 (B), U4.21 (A10)
unnamed: R10.2, SW2.2 (B), U4.23 (A11)
unnamed: U1.2 (Q0), U4.4 (A6)
unnamed: U1.5 (Q1), U4.6 (A4)
unnamed: U1.6 (Q2), U4.8 (A2)
unnamed: U1.9 (Q3), U4.10 (A0)
unnamed: U1.12 (Q4), U4.9 (A1)
unnamed: U1.15 (Q5), U4.7 (A3)
unnamed: U1.16 (Q6), U4.5 (A5)
unnamed: U1.19 (Q7), U4.3 (A7)
unnamed: U2.2 (CP), U5.3 (Q)
unnamed: U2.14 (Q0), U3.1 (A0), U4.25 (A8)
unnamed: U2.13 (Q1), U3.2 (A1), U4.24 (A9)
unnamed: C5.1, U5.5 (CV)
unnamed: R11.1, R12.2, U5.7 (DIS)
unnamed: C6.1, RV1.2, U5.2 (TR), U5.6 (THR)
unnamed: R1.1, U6.7 (A), U7.7 (A), U8.7 (A), U9.7 (A)
unnamed: R2.1, U6.6 (B), U7.6 (B), U8.6 (B), U9.6 (B)
unnamed: R3.1, U6.4 (C), U7.4 (C), U8.4 (C), U9.4 (C)
unnamed: R4.1, U6.2 (D), U7.2 (D), U8.2 (D), U9.2 (D)
unnamed: R8.1, U6.5 (DP), U7.5 (DP), U8.5 (DP), U9.5 (DP)
unnamed: R5.1, U6.1 (E), U7.1 (E), U8.1 (E), U9.1 (E)
unnamed: R6.1, U6.9 (F), U7.9 (F), U8.9 (F), U9.9 (F)
unnamed: R7.1, U6.10 (G), U7.10 (G), U8.10 (G), U9.10 (G)
~WO: D1.1 (K), J2.14, U1.1 (~E)
